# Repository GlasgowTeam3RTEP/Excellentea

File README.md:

# Description

Excellentea is an automatic tea maker. The user can operate the machine remotely through an online interface. 
In other words, you can order your tea, by chosing from several modes, as you leave work and find it ready when you get home. 
An LCD display provides feedback of the progress status. 

# Installation

## Prerequisites
The application requires the user to have Apache and php installed on their Raspberry Pi. Use your favourite package manager to install the packages _apache2_ and _php_ or, alternatively, open the terminal and use the commands below.
```
sudo apt-get update
sudo apt-get install apache2 php libapache2-mod-php -y
```
The One-wire and I2C protocols must be activated for the application to work. Run the following command:
```
sudo raspi-config
```
and navigate to _Interfacing options_ to enable _I2C_ and _1-Wire_.

## Installation procedure
Clone the repository to your Raspberry Pi and run the following commands:
```
./configure
make
make install
```
Initialise and start the apache web interface (change the default pi with your user name):
```
sudo chown -R pi /var/www/html/
rm /var/www/html/index.html
cp GUI/* /var/www/html/
sudo reboot
```
Find your local IP with:
```
hostname -I
```
The program can then be started by running the command
```
sudo excellentea
```
from the terminal, and the web interface will be available at the IP address found previously. The web interface can then be accessed by external hosts by enabling router port forwarding.

# Usage
[//]: # (instruct other people on how to use your project after they’ve installed it)

1. Load your cup with water

2. Load your tea infuser with the tea of your choice

3. Activate the tea maker from the online user interface

4. Choose the brewing mode of your tea

5. Wait...tea is ready:)

Watch Excellentea in action:
<p align="center">

</p>

# Configuration
An in-depth description of the project can be found on our [wiki](https://github.com/GlasgowTeam3RTEP/Excellentea/wiki). The following sections will briefly describe the main components and their implementation in the overall design. 

## Hardware

### Key components
- 1 Raspberry PI microcontroller board (tested on version 3 Model B)
- 1 Stepper motor (MIKROE-1530)
- 1 Digital temperature sensor (ds18b20)
- 12V DC power supply 
- 1 heating element (12V) (B004O8BGXE)
- 1 tea infuser 
- 1 reed float sensor (59630)
- 2 Darlington transistor array (ULN2803A)
- LCD
- 2 N-channel logic-level MOSFET (FQP30N06L)
- MOSFET heat sink (507222B00000G)

### Additional components
The project also requires standard passive components (e.g. resistors), prototyping tools (e.g. breadboard/pcb) and materials for the encasing. Check out our [wiki](https://github.com/GlasgowTeam3RTEP/Excellentea/wiki) for details. 

### Protocol
The digital temperature sensor DS18B20 communicates with the board through the one-wire protocol on pin 7 (BCM4). The reed float sensor only outputs two-states so a communication protocol is not required. 

## Software
The software was written to reflect the data flow depicted below. The float switch is used as a safety feature to ensure that the heating element cannot be switched on in the absence of water. Once the cup is full of water, the program will wait for a user interaction through the web interface. The main program will receive the signal to initiate the tea making procedure, using a temporary communication file, with two main parameters, the brewing temperature and the brewing time. The heating element is turned on and the temperature is monitored periodically via the sensor on the One-wire bus. Once the temperature reaches the desired value, the heating element is switched off and the preloaded tea infuser is lowered by the stepper motor. Once the desired brewing time has elapsed, the stepper motor rewinds the strainer and the tea is ready. Full software documentation can be found [here](https://glasgowteam3rtep.github.io/Excellentea/).

# Authors
* [**Andrea Spanou**](https://github.com/andreaspanou) - *Initial work* 
* [**Ciaran McGeady**](https://github.com/CiaranAnthony) - *Initial work*
* [**Simone Marcigaglia**](https://github.com/SimoneMarcigaglia) - *Initial work*

See also the list of [contributors](https://github.com/GlasgowTeam3RTEP/ExcellenTea/contributors) who participated in this project. Check out our [Twitter](https://twitter.com/Excellentea1) page to be up-to-date with the latest developments!

# Contributing

Please read [CONTRIBUTING.md](CONTRIBUTING.md) for details on our code of conduct, and the process for submitting pull requests to us.

# License

This project is licensed under the MIT License - see the [LICENSE](LICENSE) file for details.

# Acknowledgments

We would like to thank the weather in Glasgow for making us think about tea all the time.

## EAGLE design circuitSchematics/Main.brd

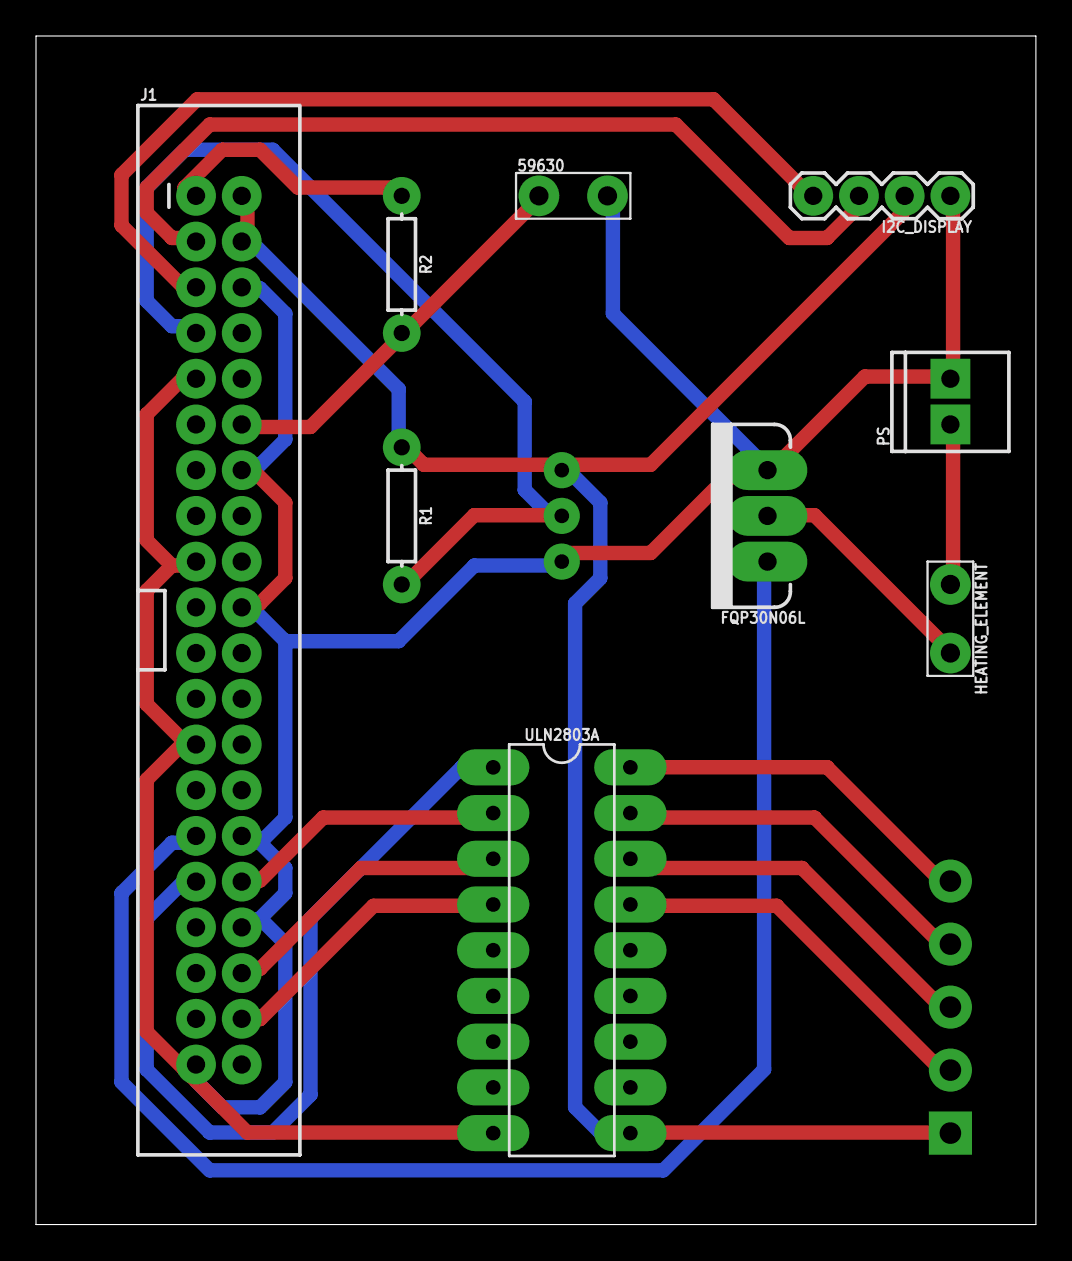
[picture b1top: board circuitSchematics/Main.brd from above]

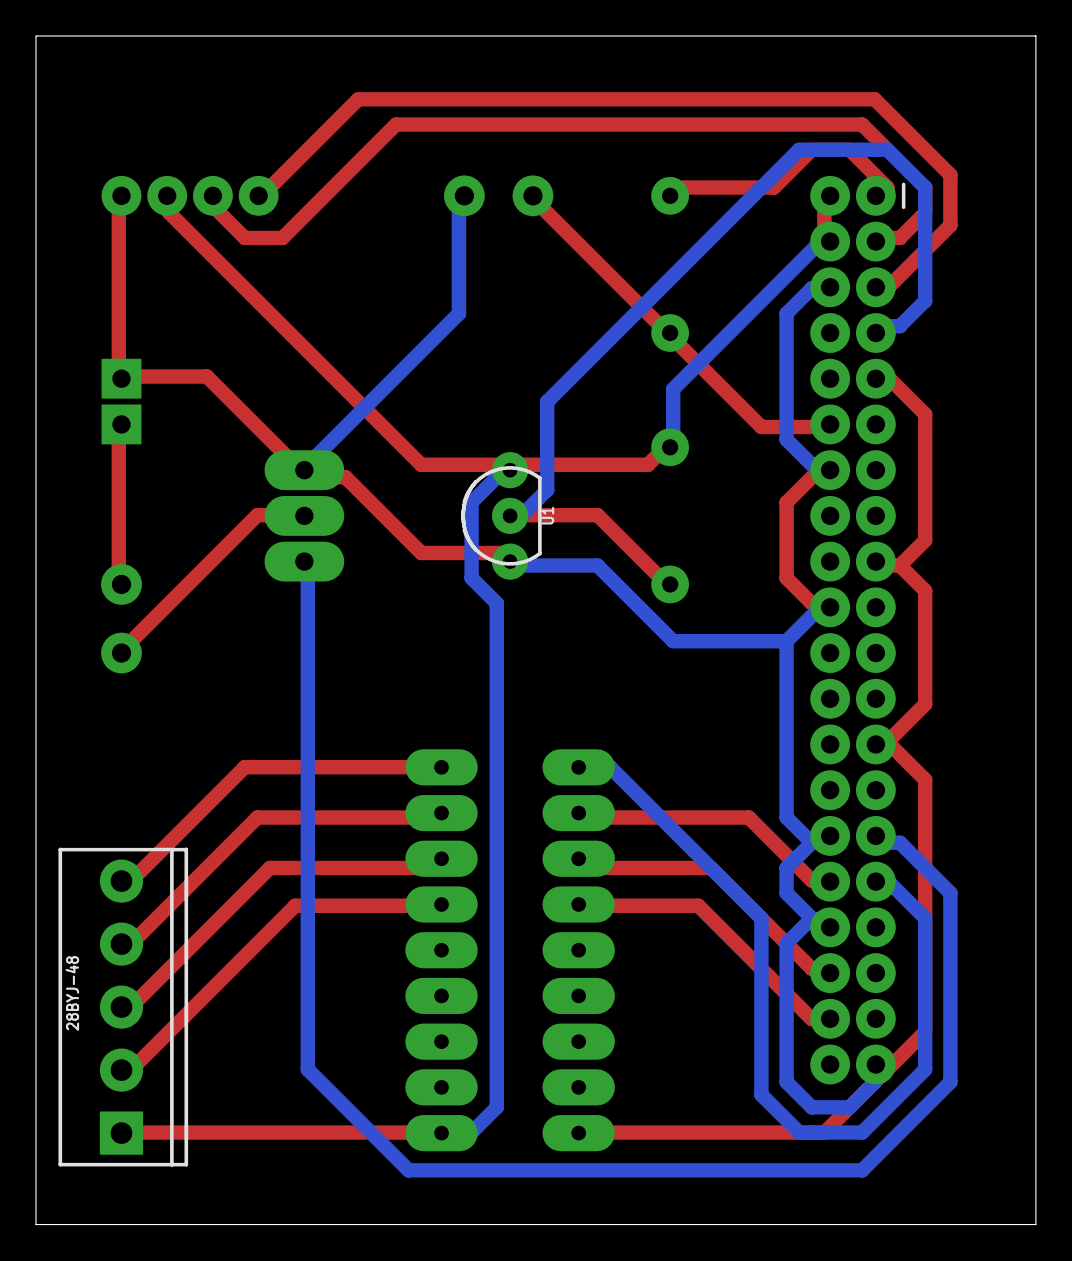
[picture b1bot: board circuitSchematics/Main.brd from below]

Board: 2 copper layers, 55.5 x 66.0 mm, 11 parts (2 on the bottom side), 18 nets.

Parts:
28BYJ-48: SCREWTERMINAL-3.5MM-5
59630: 1X02_BIG
FQP30N06L: 60V/32A/35mΩ; TO220V
HEATING_ELEMENT: 1X02_BIG
I2C_DISPLAY: 1X04
J1: RASPBERRYPI-40-PIN-GPIO_PTH; 2X20_SHROUDED
PS: Vin; 1X02_2.54_SCREWTERM
R1: 4K7; AXIAL-0.3
R2: 10k; AXIAL-0.3
U1: DS18B20; TO-92-AMMO
ULN2803A: DIL18

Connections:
3V3: J1.1, R2.P$1
5V: 28BYJ-48.1, I2C_DISPLAY.2, J1.2, J1.4, R1.P$1, U1.3, ULN2803A.10
12V: HEATING_ELEMENT.P$1, PS.P2
DQ: J1.7, R1.P$2, U1.2
GND: 59630.P$2, FQP30N06L.3, I2C_DISPLAY.1, J1.6, J1.9, J1.14, J1.17, J1.20, J1.25, J1.30, J1.34, J1.39, PS.P1, U1.1, ULN2803A.9
unnamed: J1.31, ULN2803A.1
unnamed: FQP30N06L.1, J1.29
unnamed: J1.36, ULN2803A.3
unnamed: J1.38, ULN2803A.4
unnamed: FQP30N06L.2, HEATING_ELEMENT.P$2
unnamed: J1.32, ULN2803A.2
unnamed: 28BYJ-48.5, ULN2803A.18
unnamed: 28BYJ-48.4, ULN2803A.17
unnamed: 28BYJ-48.3, ULN2803A.16
unnamed: 28BYJ-48.2, ULN2803A.15
SCL: I2C_DISPLAY.4, J1.5
SDA: I2C_DISPLAY.3, J1.3
WS: 59630.P$1, J1.12, R2.P$2

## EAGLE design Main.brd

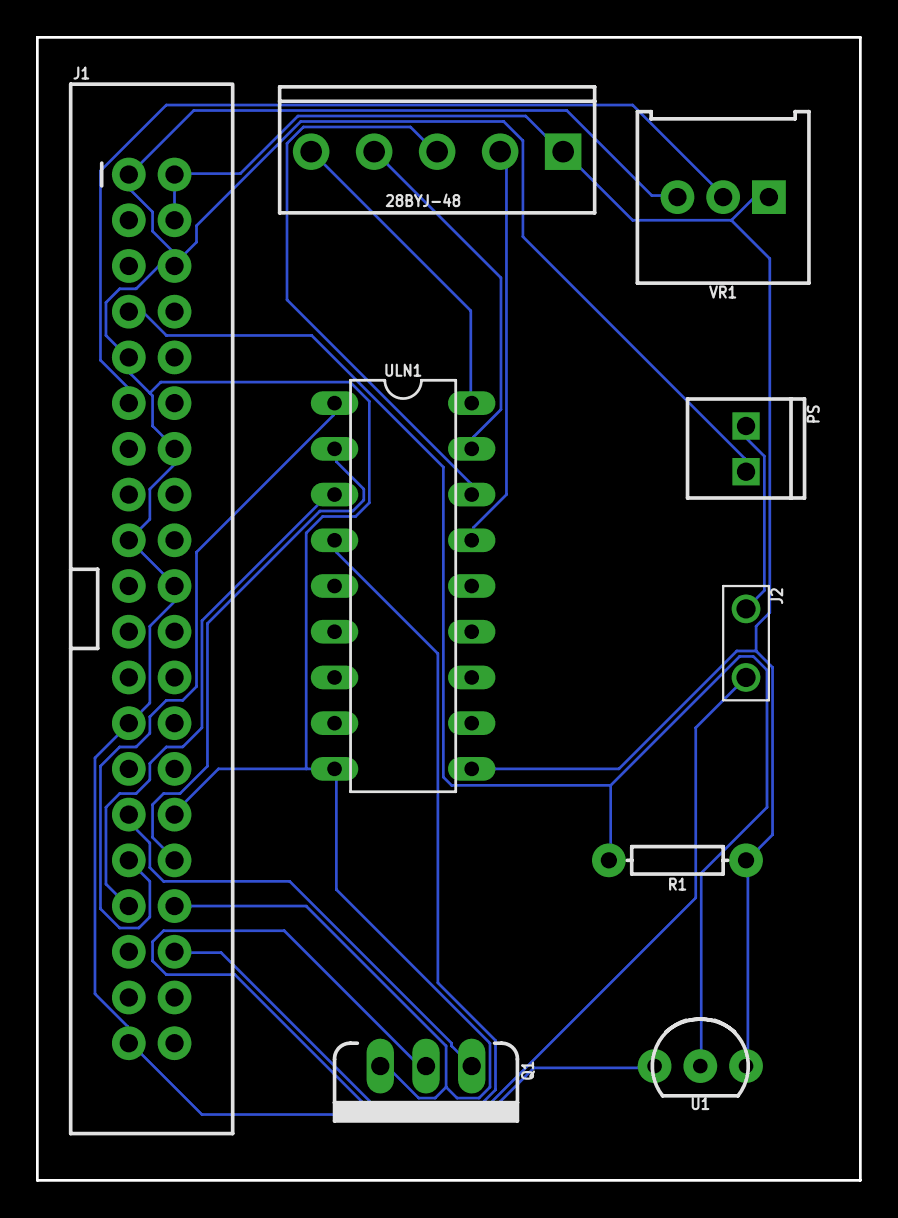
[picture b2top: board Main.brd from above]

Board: 2 copper layers, 45.7 x 63.5 mm, 9 parts (0 on the bottom side), 15 nets.

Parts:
28BYJ-48: SCREWTERMINAL-3.5MM-5
J1: RASPBERRYPI-40-PIN-GPIO_PTH; 2X20_SHROUDED
J2: Heating_element; 1X02_BIG
PS: Vin; 1X02_2.54_SCREWTERM
Q1: 60V/32A/35mΩ; TO220V
R1: 4K7; AXIAL-0.3
U1: DS18B20; TO-92-AMMO
ULN1: DIL18
VR1: 10k; TRIMPOT-PTH-3386U

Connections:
5V: 28BYJ-48.1, J1.2, J1.4, R1.P$1, U1.3, ULN1.10, VR1.1
GND: J1.1, J1.6, J1.9, J1.14, J1.17, J1.20, J1.25, J1.30, J1.34, J1.39, PS.P1, Q1.3, U1.1, ULN1.9, VR1.3
unnamed: J1.7, R1.P$2, U1.2
unnamed: J1.31, ULN1.1
unnamed: J1.29, Q1.1
unnamed: J1.33, ULN1.3
unnamed: J1.11, VR1.2
unnamed: J2.P$2, Q1.2
unnamed: J1.32, ULN1.2
unnamed: J1.36, ULN1.4
unnamed: 28BYJ-48.5, ULN1.18
unnamed: 28BYJ-48.4, ULN1.17
unnamed: 28BYJ-48.3, ULN1.16
unnamed: 28BYJ-48.2, ULN1.15
VCC_12V: J2.P$1, PS.P2

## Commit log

2018-02-11 Update README.md
    Added and completed some headings
2018-02-14 Updated README
    Rearranged sections
2018-02-14 Added Circuit schematics and PCB design
2018-02-14 Updated promo video link
2018-03-13 Created image folder and added Banner.png to the readme file
2018-03-13 Set theme jekyll-theme-architect
2018-03-13 Scaled banner and updated Readme file
2018-03-13 Fixed first heading
2018-03-14 Added classes (tea, stepper, sensor and ds18b20), makefile and configure file
2018-03-15 Moved circuit and board schematics to subfolder
2018-03-15 Added installation instructions
2018-03-15 Added autoconf files
2018-03-19 Added class documentation
2018-03-21 Modified banner
2018-03-22 Updated circuit schematics
2018-03-22 Added float sensor and I2C LCD
2018-03-22 Rearranged classes under single folder
2018-03-23 Renamed folders for consistency
2018-03-23 Updated images and user operation
2018-03-23 Capitalized classes for consistency
2018-03-23 Added logo
2018-03-23 Removed unnecessary files
2018-03-23 Added doxygen documentation
2018-03-23 Moved documentation to webpage
2018-03-23 Added class to control heating element
2018-03-24 Create Empty
2018-03-24 Added drawing for 3D printed part
2018-03-24 correction needed
2018-03-24 corrected drawing
2018-03-24 Added data flow diagram
2018-03-24 added php file checking the status
2018-03-24 added php file for activation control
2018-03-25 Added main file for GUI
2018-03-26 Added I2C lcd control and multi-thread programming
2018-03-26 Implemented multi-thread programming
2018-03-26 Improved documentation
2018-03-26 Added thread classes and LCD control
2018-03-26 Converted drawings to png
2018-03-26 Moved website to gh-pages branch
2018-03-26 Converted PCB design to png
2018-03-26 Updated installation procedure and structure
2018-03-26 Added link for software documentation
2018-03-26 Moved data flow
2018-03-26 updated GUI files
2018-04-03 Removed AJAX from web interface
2018-04-04 Added webGUI comm and modified temperature feedback
2018-04-09 Added user control interface
2018-04-09 Deleted unnecessary files
2018-04-09 Removed multi-thread programming
2018-04-09 Removed multi-thread
2018-04-09 Removed files left over from previous versions
2018-04-10 Added messages for easy debugging
2018-04-10 Added brewing countdown timer
2018-04-13 updated intro
2018-04-13 upadeted software section
2018-04-13 Changed pins to match circuit shematics
2018-04-16 Added link to video and thumbnail

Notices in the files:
parts and their libraries:
SparkFun-Connectors: Licensing: Creative Commons ShareAlike 4.0 International - https://creativecommons.org/licenses/by-sa/4.0
